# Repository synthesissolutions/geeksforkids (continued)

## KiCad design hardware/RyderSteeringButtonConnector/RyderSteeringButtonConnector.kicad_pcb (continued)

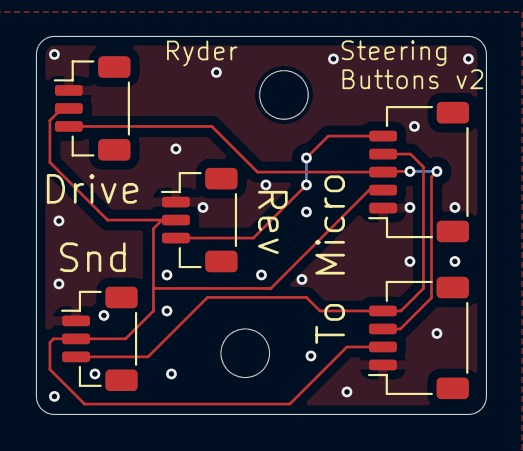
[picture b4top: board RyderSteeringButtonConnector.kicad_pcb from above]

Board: 2 copper layers, 25.0 x 21.0 mm, 7 parts (0 on the bottom side), 5 nets.

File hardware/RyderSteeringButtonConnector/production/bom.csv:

Designator,Footprint,Quantity,Value,LCSC Part #
J1,JST_SH_SM04B-SRSS-TB_1x04-1MP_P1.00mm_Horizontal,1,Conn_01x04_Pin,C160403
J2,JST_SH_SM05B-SRSS-TB_1x05-1MP_P1.00mm_Horizontal,1,Conn_01x05_Pin,C136657
"J3, J4, J5",JST_SH_BM03B-SRSS-TB_1x03-1MP_P1.00mm_Vertical,3,Conn_01x03_Pin,C160389

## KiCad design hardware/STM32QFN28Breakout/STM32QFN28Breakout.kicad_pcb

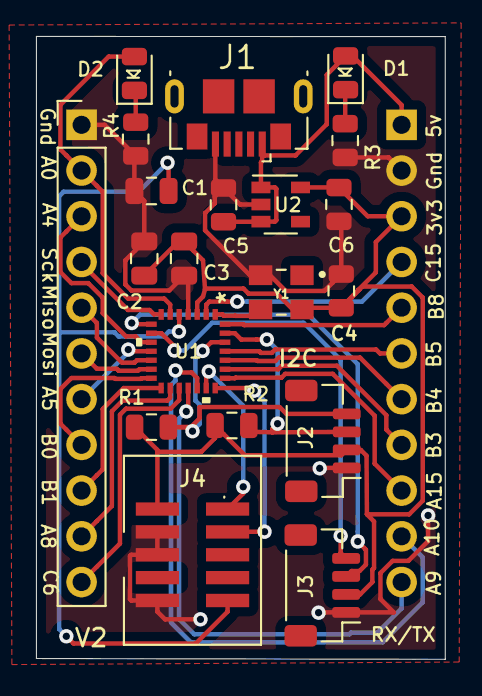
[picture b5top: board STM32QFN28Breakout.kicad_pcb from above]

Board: 2 copper layers, 22.7 x 34.6 mm, 21 parts (0 on the bottom side), 31 nets.

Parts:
C1, C2, C4: 100nF; C_0805_2012Metric
C3: 10uF; C_0805_2012Metric
C5, C6: 1uF; C_0805_2012Metric
D1: Power LED; LED_0805_2012Metric
D2: User LED; LED_0805_2012Metric
J1: USB3076-XX-X_REVC; USB_Micro-B_GCT_USB3076-30-A
J2, J3: Conn_01x04_Male; JST_SH_BM04B-SRSS-TB_1x04-1MP_P1.00mm_Vertical
J4: Conn_ARM_JTAG_SWD_10; JTAG_SWD_SMD
J5, J6: Conn_01x11_Male; PinHeader_1x11_P2.54mm_Vertical
R1, R2: 10K; R_0805_2012Metric
R3: 1K; R_0805_2012Metric
R4: 470; R_0805_2012Metric
U1: STM32G031F4Px; STM32G031G8U6
U2: AP2112K-3.3; SOT-23-5
Y1: ECS-3225MVQ-160-BP-TR; OSC_ECS-3225MVQ-160-BP-TR

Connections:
+3V3: C2.1, C3.1, C4.2, C6.2, J2.2, J3.2, J4.1, J6.3, R1.2, R2.2, U1.3, U2.5, Y1.4
+5V: C5.1, D1.2, J1.1, J6.1, U2.1, U2.3
/RESET: C1.1, J4.10, U1.5
GND: C1.2, C2.2, C3.2, C4.1, C5.2, C6.1, J1.5, J2.1, J3.1, J4.3, J4.5, J4.9, J5.1, J6.2, R3.1, R4.2, U1.4, U2.2, Y1.2
MISO: J5.5, U1.12
MOSI: J5.6, U1.13
unnamed: D1.1, R3.2
unnamed: D2.1, R4.1
OscillatorIn: U1.1, Y1.3
PA0: D2.2, J5.2, U1.6
PA4: J5.3, U1.10
PA5: J5.7, U1.11
PA8: J5.10, U1.16
PA9: J6.11, U1.18
PA10: J6.10, U1.19
PA15: J6.9, U1.22
PB0: J5.8, U1.14
PB1: J5.9, U1.15
PB3: J6.8, U1.23
PB4: J6.7, U1.24
PB5: J6.6, U1.25
PB8: J6.5, U1.28
PC6: J5.11, U1.17
PC15: J6.4, U1.2
RX: J3.4, U1.9
SCK: J5.4, U1.7
SCL: J2.4, R1.1, U1.26
SDA: J2.3, R2.1, U1.27
SWCLK: J4.4, U1.21
SWDIO: J4.2, U1.20
TX: J3.3, U1.8
